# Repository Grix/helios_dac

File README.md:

# Helios Laser DAC
Digital to Analog Converter for laser projectors.

* https://bitlasers.com/helios-laser-dac/

Open source, low cost USB DAC for the ISP-DB25 (ILDA) laser protocol. Allows you to control an ILDA laser projector via computer over USB. Supports lots of third party software (see link above). This repository consists of:
* SDK for supporting the Helios USB and IDN DACs in your software (with examples in C++, Python and C#/.NET)
* Hardware (PCB schematic in KiCAD)
* Firmware (Atmel Studio project)
* Extras (firmware update tool, media etc.)

## Developer guide

#### Third party software integration

Navigate to the folder "sdk" to find the relevant code for interfacing with the Helios DAC in your software, and a readme with more detailed usage instructions. 

NEW: The C++ sdk has been updated to include IDN network support. This means that if you implement/update the Helios library in your application, it will also seamlessly enable support for any other network DAC using the IDN protocol, including the Helios OpenIDN adapter, StageMate ISP, and upcoming Helios products.
**Other libraries than the C++ one has not yet been updated with IDN support.**

The reference SDK is written in C++, in the subfolder "cpp". But libraries with exported functions that you can call from many languages such as python or C# are available, documented in HeliosDacAPI.h. You can also find examples of usage in the examples folder.

The C++ code depends on libusb. You can use the included libusb binary libraries for Win32, Mac or Linux, or you can build your own. You can find the libusb source on libusb.info, or binaries on https://sourceforge.net/projects/libusb/files/libusb-1.0/

If you wish to use the shared library, there are ready-made builds for Win32 (.dll) and 64-bit linux (.so) in the sdk folder. NB: Only the Windows binary is guaranteed to be up to date. For Mac and Linux it is recommended to build your own or use the C++ classes.

New: There is a native .NET library with example code in sdk/dotnet. HOWEVER, the C# library is not yet updated with IDN (network) support, so it is not recommended for general use yet.

If you are adding support for the Helios in your program, let me know and I can link it on the Helios' website.

Steps to compiling shared library (.so) for Linux based systems yourself is below. For macOS, try replacing ".so" with ".dylib". For Windows, there is a Visual Studio project in the source directory.

```shell
g++ -Wall -std=c++14 -fPIC -O2 -c HeliosDacAPI.cpp
g++ -Wall -std=c++14 -fPIC -O2 -c HeliosDac.cpp
g++ -shared -o libHeliosDacAPI.so HeliosDacAPI.o HeliosDac.o libusb-1.0.so
```
To use the device on Linux you either need root privileges or need to set up udev rules (see https://bitlasers.com/helios-laser-dac/). On Windows and Mac it should be plug and play.

A more detailed guide for compiling for Raspberry Pi (Linux ARM) is also available in the docs folder.

#### Hardware and firmware modification

The PCB is drawn in Kicad. The firmware is written and built with Atmel Studio for the ATSAM4S2B microcontroller.
**NB: The license for the hardware and firmware, unlike the software, does not permit the sale of manufactured units.**
New firmware can be uploaded to the device over USB. To do this, you must reset the "GPNVM1" bit in the flash memory, which will make the microcontroller boot to the SAM-BA bootloader. You can do this by sending a special interrupt packet to the DAC. You can then access the flash using Atmel's SAM-BA software or BOSSA. There is an automatic tool for firmware updating:

* Download the firmware updating tool (only for Windows as of now, Mac/Linux partially done): utility/FirmwareUpdater/cli/firmwareupdater_script.zip
* Unzip, plug in the DAC and run the file "flash.bat".
* Follow the instructions on the screen (you may need to unplug and replug the device a couple of times as instructed).

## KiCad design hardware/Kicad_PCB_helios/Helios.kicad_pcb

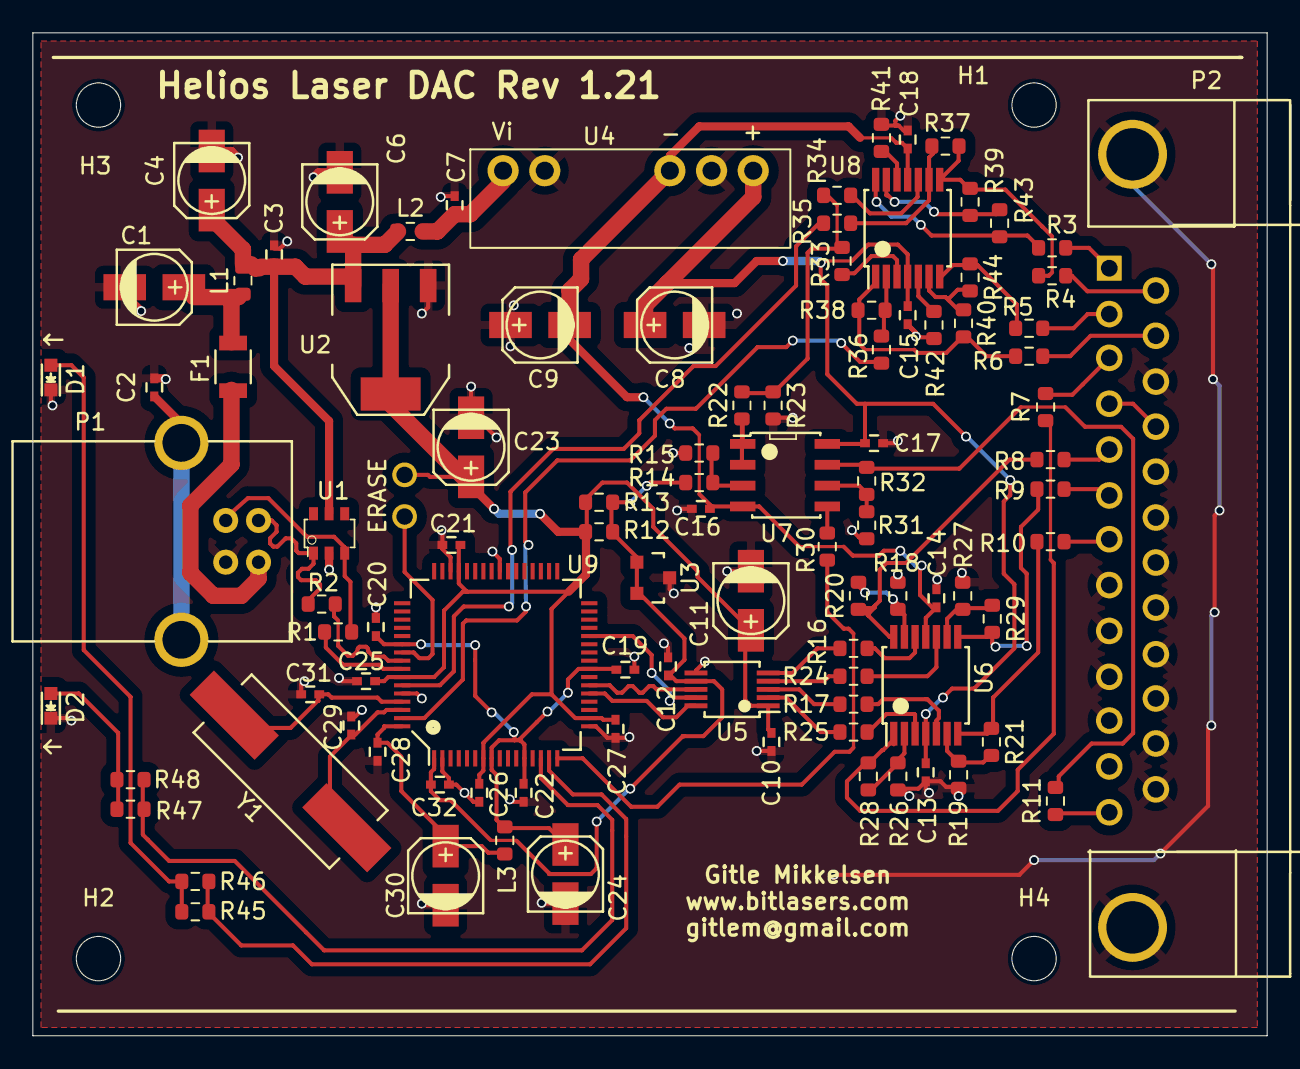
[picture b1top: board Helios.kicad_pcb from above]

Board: 2 copper layers, 75.2 x 61.1 mm, 102 parts (0 on the bottom side), 50 nets.

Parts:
C1, C4, C6, C8, C9, C11, C23, C24, C30: 4.7uF; c_elec_4x5.3
C2, C3, C7, C10, C13, C14, C15, C16, C17, C18, C19, C20, C21, C22, C25, C26, C27, C28: 100nF; C_0402
C12, C29, C31, C32: 13pF; C_0402
D1, D2: Led_Small; LED_0603
ERASE: CONN_01X02; PINHEAD1-2
F1: F_Small; R_1206
H1, H2, H3, H4: MountingHole; MountingHole_2.7mm_M2.5
L1, L2, L3: FILTER; R_0603_1608Metric
P1: USB_B
P2: CONN_01X25-SHIELD; DB25
R1, R2: 27; R_0603_1608Metric
R3, R4, R5, R6, R7, R8, R9, R10, R11, R12, R13: 150; R_0603_1608Metric
R14, R15, R18, R19, R20, R21, R23, R26, R27, R28, R29, R31, R37, R38, R39, R40, R43, R44: 10k; R_0603_1608Metric
R16, R17, R24, R25, R30, R32, R41, R42: 5.11k; R_0603_1608Metric
R22, R33, R34, R35, R36, R45, R46, R47, R48: 1.65k; R_0603_1608Metric
U1: IP4220CZ6; SOT457
U2: AP2114; SOT-223
U3: AN431B; SOT-23
U4: CRV1DxxxxSC
U5: DAC084S085C; MSOP-10_3x3mm_Pitch0.5mm
U6, U8: TL084_v; TSSOP-14_4.4x5mm_Pitch0.65mm
U7: LM358; SOIC-8_3.9x4.9mm_Pitch1.27mm
U9: ATSAM4S; LQFP-64_10x10mm_Pitch0.5mm
Y1: 16MHz 18pF; Crystal_HC49-SD_SMD

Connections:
/2.5V: C12.2, C32.1, R12.2, R13.2, R14.1, U3.1 (Cathode), U3.2 (Ref), U5.7 (Vrefin), U9.1 (ADVREF)
/3.3V: C10.1, C11.1, C21.1, C23.1, C25.1, C26.1, C27.1, ERASE.2, R12.1, R13.1, U2.2 (VOUT), U5.1 (Va), U9.7 (VDDIN), U9.18 (VDDIO), U9.45 (VDDIO), U9.58 (VDDIO)
/!SYNC: U5.9 (!SYNC), U9.28 (PA11/PGMM3)
/+9V: C8.1, C13.2, C15.2, C17.2, U4.7 (Vout+), U6.4 (Vcc), U7.8 (V+), U8.4 (Vcc)
/+B: R10.2, R21.1, U6.7 (Out)
/+G: R9.2, R29.1, U6.8 (Out)
/+Int: R7.2, R28.1, U6.1 (Out)
/+R: R8.2, R20.1, U6.14 (Out)
/+X: R3.2, R43.1, U8.14 (Out)
/+Y: R5.2, R44.1, U8.7 (Out)
/-9V: C9.2, C14.2, C16.2, C18.2, U4.5 (Vout-), U6.11 (Vee), U7.4 (V-), U8.11 (Vee)
/-X: R4.2, R37.1, R39.2, U8.8 (Out)
/-Y: R6.2, R38.1, R40.2, U8.1 (Out)
/Amplifiers/Offset: R22.2, R23.1, R33.2, R34.2
/B: R17.2, U5.3 (Voutb)
/D+: P1.3 (D+), R1.2, U1.3 (IO2)
/D-: P1.2 (D-), R2.2, U1.1 (IO1)
/G: R24.2, U5.4 (Voutc)
/Int: R25.2, U5.2 (Vouta)
/Interlock: P2.4, P2.17
/Microcontroller/D+: R1.1, U9.57 (DDP/PB11)
/Microcontroller/D-: R2.1, U9.56 (DDM/PB10)
/Microcontroller/ERASE: ERASE.1, U9.55 (ERASE/PB12)
/Microcontroller/PA22: R47.1, R48.1, U9.14 (PA22/PGMD10/AD9)
/Microcontroller/PA23: R45.1, R46.1, U9.15 (PA23/PGMD11)
/Microcontroller/VDDOUT: C19.1, C20.1, C22.1, C24.1, L3.1, U9.8 (VDDOUT), U9.12 (VDDCORE), U9.24 (VDDCORE), U9.54 (VDDCORE)
/Microcontroller/VDDPLL: C28.1, C30.1, L3.2, U9.64 (VDDPLL)
/Microcontroller/XIN: C29.1, U9.62 (XIN/PGMCK/PB9), Y1.1
/Microcontroller/XOUT: C31.1, U9.61 (XOUT/PB8), Y1.2
/R: R16.2, U5.5 (Voutd)
/SCLK: U5.10 (SCLK), U9.21 (PA14/PGMD2)
/Shutter: R30.2, U9.16 (PA20/PGMD8/AD3)
/Shutter_Out: R11.2, R32.1, U7.7
/VCC: C3.1, C4.1, C6.1, L1.2, L2.1, U1.5 (Vp), U2.3 (VIN)
/X: R35.2, U9.59 (PB13/DAC0)
/Y: R36.2, U9.63 (PB14/DAC1)
GND: C1.2, C2.2, C3.2, C4.2, C6.2, C7.2, C8.2, C9.1, C10.2, C11.2, C12.1, C13.1, C14.1, C15.1, C16.1, C17.1, C18.1, C19.2, C20.2, C21.2, C22.2, C23.2, C24.2, C25.2, C26.2, C27.2, C28.2, C29.2, C30.2, C31.2, C32.2, D1.1 (K), D2.1 (K), P1.4 (GND), P2.8, P2.9, P2.10, P2.11, P2.16, P2.18, P2.19, P2.20, P2.21, P2.22, P2.23, P2.24, P2.25, P2.26 (Shield), R15.2, R18.2, R19.2, R23.2, R26.2, R27.2, R31.1, R41.2, R42.2, U1.2 (GND), U2.1 (GND), U3.3 (Anode), U4.2 (GND), U4.6 (Vout0), U5.6 (GND), U9.2 (GND), U9.17 (GND), U9.40 (TST), U9.46 (GND), U9.60 (GND)
unnamed: C1.1, F1.2, L1.1
unnamed: F1.1, P1.1 (VCC)
unnamed: C2.1, P1.5 (shield)
unnamed: P2.1, R3.1
unnamed: P2.2, R5.1
unnamed: P2.3, R7.1
unnamed: P2.5, R8.1
unnamed: P2.6, R9.1
unnamed: P2.7, R10.1
unnamed: P2.13, R11.1
unnamed: P2.14, R4.1
unnamed: P2.15, R6.1
unnamed: C7.1, L2.2, U4.1 (Vin)

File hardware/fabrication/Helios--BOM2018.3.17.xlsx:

BOM
Manufacturer | Manufacturer Part Number | Designator | Qty | Description | Case | SMD ,BGA,LLC(QFN),OR TH | Top/Bottom | points | Total points | Note | Comments
Lelon | VE-4R7M1HTR-0405 | C1, C4, C6, C8, C9, C11, C23, C24, C30 | 9.0 | 4.7uF,50V,20%,4.00mmD*5.30mmH,2000Hrs@85℃ | 4.30mmL*4.30mmW | SMD | Top | 2.0 | 18
Yageo | CC0402KRX7R8BB104 | C2, C3, C7, C10, C13, C14, C15, C16, C17, C18, C19, C20, C21, C22, C25, C26, C2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 | 18.0 | 100nF,25V,10%,X7R,0402 | 0402 | SMD | Top | 2.0 | 36
Murata | GRM1555C1H130JA01D | C12, C29, C31, C32 | 4.0 | 13pF,50V,5%,C0G,0402 | 0402 | SMD | Top | 2.0 | 8
Yageo | RC0603JR-0727RL | R1, R2 | 2.0 | 27R,5%,1/10W,0603 | 0603 | SMD | Top | 2.0 | 4
Yageo | RC0603JR-07150RL | R3, R4, R5, R6, R7, R8, R9, R10, R11, R12, R13 | 11.0 | 150R,5%,1/10W,0603 | 0603 | SMD | Top | 2.0 | 22
Yageo | RC0603FR-071K65L | R22, R33, R34, R35, R36, R45, R46, R47, R48 | 9.0 | 1.65K,1%,1/10W,0603 | 0603 | SMD | Top | 2.0 | 18
Yageo | RC0603FR-075K11L | R32, R16, R17, R24, R25, R30, R41, R42 | 8.0 | 5.11K,1%,1/10W,0603 | 0603 | SMD | Top | 2.0 | 16
Yageo | RT0603BRD0710KL | R14, R15, R18, R19, R20, R21, R23, R26, R27, R28, R29, R31, R37, R38, R39, R40,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 | 18.0 | 10K,0.1%,1/10W,0603 | 0603 | SMD | Top | 2.0 | 36
ouleite | OLTEUSBFB-588 | P1 | 1.0 | USB,B type,90° | 16.30mmL*12.15mmW*11.00mmH | TH | Top | 6.0 | 6
TAD | DB-25F | P2 | 1.0 | Female,25 holes,90° | 53.10mmL*18.50mmW*12.55mmH | TH | Top | 27.0 | 27
NXP Semiconductors | IP4220CZ6,125 | U1 | 1.0 | IP4220CZ6,125,6-TSOP | 6-TSOP | SMD | Top | 6.0 | 6
Diodes Incorporated | AP2114H-3.3TRG1 | U2 | 1.0 | AP2114H-3.3TRG1,SOT-223 | SOT-223 | SMD | Top | 4.0 | 4
Diodes Incorporated | AN431AN-ATRG1 | U3 | 1.0 | AN431AN-ATRG1,SOT-23-3 | SOT-23-3 | SMD | Top | 3.0 | 3
XP Power | ISA0512-TR | U4 | 1.0 | 4.5Vin,5.5Vout/±12Vout,1W,15.20mmL*8.30mmW*7.30mmH | 15.20mmL*8.30mmW*7.30mmH | SMD | Top | 6.0 | 6.0
Texas Instruments | DAC084S085CIMM/NOPB | U5 | 1.0 | DAC084S085CIMM/NOPB,VSSOP-10 | VSSOP-10 | SMD | Top | 10.0 | 10
STMicroelectronics | TL084IPT | U6, U8 | 2.0 | TL084IPT,TSSOP-14 | TSSOP-14 | SMD | Top | 14.0 | 28
STMicroelectronics | LM358YDT | U7 | 1.0 | LM358YDT,SO-8 | SO-8 | SMD | Top | 8.0 | 8
Atmel | ATSAM4S2BA-AU | U9 | 1.0 | ATSAM4S2BA-AU,64-LQFP | 64-LQFP | SMD | Top | 64.0 | 64
Abracon | ABLS2-16.000MHZ-D4Y-T | Y1 | 1.0 | 16MHz,18pF,HC49/US | HC49/US | SMD | Top | 2.0 | 2
Bel Fuse | 0ZCJ0050FF2G | F1 | 1.0 | 8V,500mA,1206 | 1206 | SMD | Top | 2.0 | 2
TDK Corporation | MPZ1608B471ATA00 | L1, L2, L3 | 3.0 | 470R,1A,0603 | 0603 | SMD | Top | 2.0 | 6
Kingbright | APA1606SYCK | D1, D2 | 2.0 | Yellow,2V,150mcd,2-SMD | 2-SMD | SMD | Top | 2.0 | 4

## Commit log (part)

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2016-06-30 add kicad project
2016-07-09 temp driver and 7byte point structure firmware
2016-07-14 driver finished but untested
2016-07-18 GPIO signal wiring and USB IDs
2016-07-23 redone pcb, driver and firmware working-ish
2016-07-26 rev 1.1 pcb final
2016-07-29 fix BOM error
2016-08-03 experimenting with driver
2016-08-04 capacitors wrong polarity
2016-08-08 improve driver
2016-08-13 fix color amps error
2016-08-15 removed uneccessary resistors
2016-09-21 automatic winusb installation, not tested
2016-09-22 cleanup
2016-09-24 fix Stop() bug and winusb auto install working
2016-09-27 OLSC compatible driver
2016-09-29 media folder and tweaking interrupt transfers
2016-09-30 added delayed stop timer for reliability
2016-10-01 firmware version getter + some documentation
2016-10-02 Mac libusb binaries (not tested)
2016-10-07 reorganize folders
2016-10-15 custom naming of dac firmware working
2016-10-15 driver updated to support firmware v2
2016-10-16 backwards comp. fixed
2016-10-16 binaries
2016-10-16 started automated firmware flashing app based on sam-ba
2016-10-16 updated source in root
2016-10-21 cli firmware update script
2016-10-21 zipped firmware update script
2016-10-22 bossa firmware updating tool
2016-10-23 shrunk firmware with no mlong_calls to make bossac work
2016-10-26 added some niche functions to the API
2016-10-27 libusb 1.0.21
2016-10-29 updated root sdk source folder and organized better
2016-10-30 firmware tweaks, started sdk example
2016-11-01 Read different unique id
2016-11-26 example app tests all connected DACs instead of just one
2016-11-27 delay on initialization
2016-11-27 python example
2016-11-29 compile shared object library in order to use DAC on Linux using Python
2016-12-06 fix extern c, recompile so library with libusb and HeliosDac.cpp, split python examples on linux/windows version
2016-12-12 expand REDME.md file, add instructions how compile shared library with API
2016-12-21 optionally flipped X axis
2017-01-03 readme updated
2017-01-03 documentation tweaks
2017-01-10 fix a warning
2017-01-15 fixed jitter
2017-01-17 comments cleanup
2017-02-11 notice in license
2017-02-22 working on buffered status
2017-02-22 dropouts fixed
2017-02-22 more robust status transfer polling
2017-02-24 working on backwards compatibility and better exception handling
2017-02-26 mostly finished firmware+sdk v5 but bugs remain
2017-03-02 another strategy for status caching
2017-03-04 further sdk+firmware tweaks
2017-03-04 zipped test binaries
2017-03-05 more safety
2017-03-08 some debug, and length independent intrpt in transfer queries
2017-03-09 adjust the code to run on Linux, update shared library compilation instruction
2017-03-09 move library include from .cpp to .h files
2017-03-09 more experimentation
2017-03-11 major sdk rewrite
2017-03-11 working but not in lsx
2017-03-12 sdk backwards compatibility and robustness, plus new ASF version
2017-03-12 fixed thread not quitting when dac unplugged while playing, + cleanup
2017-03-13 zipped beta firmware with updating script
2017-03-19 better documentation in sdk header files
2017-03-20 updated example app
2017-03-20 updated bugfix in cpp example app
2017-03-26 no longer need to keep points buffer from being freed prematurely
2017-03-31 timeout check [chkpoint]
2017-06-07 less cpu usage
2017-06-08 blocking of WriteFrame() optional
2017-06-09 revert to explicit status query, + cleanup
2017-06-11 fix bug causing some frame sizes to fail + erronous flag constants in header
2017-06-12 add pps compensation to bug workaround
2017-06-13 some better commenting and cleanup
2017-06-14 pull
2017-06-14 sdk v6
2017-06-14 16bit xy in sdk
2017-06-30 better adherence to C++ rules
2017-06-30 inner namegetter passing by pointer
2017-07-12 add vref params to frames
2017-07-12 change frame of size allocs to make room for vref values
2017-08-21 img and udev note
2017-10-01 info paper
2017-10-29 small readme change
2017-12-20 update msvc project to 2017, with win64 build config
2017-12-20 folder name change for msvc source
2018-04-09 EzAudDac compatible api in driver
2018-04-27 libusb integrated
2018-05-25 small changes to info document
2018-06-06 change submodule to official libusb repo
2018-07-09 stdcall get/set name for vb
2018-07-15 fixed linux python example
2018-12-05 Add unique error codes for all error conditions.
2018-12-06 Add ability to set libusb debug log level
2018-12-06 Use correct device number in call to WriteFrame()
2018-12-06 Test for GetStatus() != 1 instead of GetStatus() == 0 so that errors aren't misinterpreted as ready status. Limit to 512 calls to GetStatus() before giving up.
2018-12-07 Copy linux_example.py fix to windows_example.py
2019-01-02 docs folder
2019-05-19 fix some outdated schematics
2019-08-28 Simplification of readme
2020-04-26 Started on dotnet nuget extension
2020-05-04 Wrote writeframe and getname functions in C# library
2020-10-12 modify HeliosDac.cpp in order to compile shared library under linux
2020-11-10 Readme updates, and some tweaks in EzAudDac compatibility API
2020-11-21 Continued on .NET driver, and fixed a compile error in c++ driver in windows
2020-11-22 More work on dotnet driver.
2021-01-02 Change doc for ubuntu 20.04 at RPi
    Fix path invalid at ubuntu 20.04
2021-01-29 Fix windows python example having too many points in a frame
2021-07-15 Add new photos
2021-08-22 Add diagnostics tool for usb Helios detection
2022-02-20 Russian translation of getting started doc
2022-08-21 Fix wrong frame buffer array size in dotnet implementation (but library still not working in windows)
2022-11-19 Working .NET SDK
2022-12-15 updated docs
2023-02-24 add 64-bit version of libusb windows binaries
2023-03-31 Fix dangling libusb thread after closing devices
2023-04-01 nuget package attributes
2023-04-30 Clarifying license
2023-04-30 Spelling
2023-05-21 Update docs
2023-10-15 Updated libusb windows binaries
2023-12-09 Update explanatory comment to new libusb version
2023-12-24 USB diagnosis tool binaries
2024-09-15 small docs update
2024-09-15 rename folder
2024-09-15 Reorganize and clean up SDK folder
2024-09-15 Include IDN files
2024-09-17 Basic IDN support working
2024-09-24 Changing strategy for variable resolution frames
2024-09-25 Legacy format IDN frame writing tested to work
2024-09-27 Move code to correct place
2024-10-12 Explicitly set shutter on C# example code
2024-10-13 Fix bugs in new IDN driver
2024-10-13 Add simulated status timing to IDN driver for compatibility
2024-10-25 Add support for getting firmware version and renaming IDN dacs
2024-10-25 Add support for renaming IDN DACs and fix bugs
2024-10-26 Separate max/min frame specs for USB and IDN, with subsampling for compatibility
2024-10-26 Modernized cpp app example, and fixed some bugs in IDN driver
2024-10-27 Fix compilation error on mac
2024-10-28 Readme update for IDN
2024-10-28 Implement new function in exported API, remove OLSC, and polish
2024-10-29 Fixed ezauddac exported wrapper
2024-10-30 Polish
2024-11-02 Fix IDN not properly stopping on closing device, and polish
2024-11-04 Compile dynamic libraries
2024-11-04 Integrated IDN support (#28)
    * Include IDN files
    * Basic IDN support working
    * Changing strategy for variable resolution frames
    * Legacy format IDN frame writing tested to work
    * Move code to correct place
    * Explicitly set shutter on C# example code
2024-11-23 Fix udp send buffer not big enough on certain OSes
2024-12-04 Started switch to IDN wave mode, but buggy
2024-12-05 Improve simulated timing
2024-12-05 Fix possible wave packet with too low point count.
2024-12-07 Misc polish
2024-12-08 Improved but still not good enough jitter. Also fix duplicate servers based on unit-id
2024-12-08 Checkpoint before trying ring buffer
2024-12-09 Major refactor, glitchy still
2024-12-10 Small tweaks. Glitchy, probably race condition
2024-12-11 Finally working well
2024-12-16 Added more functions for differentiating between USB and IDN devices
2024-12-18 Fix possible crash when closing device, and unix timing
2024-12-18 Revert accidental wrong mutex
2024-12-19 Sort device list and fix another possible crash when closing IDN device
2024-12-20 More tolerant timing if buffer underrun a little bit
2024-12-20 Don't count late waits when no frame is playing
2024-12-21 Fix possible stuck state after buffer underrun
2024-12-30 Final touches on documentation/comments
2025-01-03 Change IDN to wave mode, and more (#29)
    * Started switch to IDN wave mode, but buggy
    * Improve simulated timing
    * Fix possible wave packet with too low point count.
    * Misc polish
    * Improved but still not good enough jitter. Also fix duplicate servers based on unit-id
    * Checkpoint before trying ring buffer
2025-01-05 Fix some rare memory leaks and better syntax
2025-01-05 Fix potential race condition leading to division by zero
2025-01-13 rename plt-posix.c to .cpp
2025-01-13 rename plt-posix.c to .cpp (#30)
2025-04-01 Updated compile instructions for linux
2025-05-08 Fix visual studio windows example referencing posix-specific files
2025-06-23 Fix error in command for building on linux
2025-10-27 Rescanning
2025-10-27 Revert libusb update
2025-10-27 Better sleep in hot-plug example code
2025-10-27 Rescan fixes
2025-11-02 Don't verify connection during rescan if USB device was recently active
2025-11-28 Fix potential exception if rescanning usb after only scanning network initially
2025-11-28 Fix bug disrupting IDN timing if rescanning
2025-12-08 switch to new PSU on PCB. Fix bug in sdk example c++ app
2025-12-22 Update HeliosDac.cpp
    Fix crash if only opening USB
2026-01-01 Improve comments in driver and example code
2026-01-20 Award humble brag
2026-01-26 Fix bug with D1 in pcb
2026-02-01 rohs compliance doc
2026-02-17 Minor changes to fix compilation on MacOS
2026-03-10 Revert macOS specific packet handling
    Removed macOS specific handling for oversized UDP datagrams and adjusted logic for increasing max UDP packet size.
2026-03-11 fix(idn): initialize new IDN contexts in Unix scan path
    Restore missing Unix-side initialization of `isStoppedOrTimeout`,
    `packetNumFragments`, and `unitId` when creating IDN contexts.
    This matches Windows behavior and fixes rescan/device matching and
    initial packet sizing issues introduced during the rescan refactor.
2026-03-11 Minor changes to fix compilation on MacOS (#35)
    * Minor changes to fix compilation on MacOS
    * Revert macOS specific packet handling
    Removed macOS specific handling for oversized UDP datagrams and adjusted logic for increasing max UDP packet size.
    * fix(idn): initialize new IDN contexts in Unix scan path
    Restore missing Unix-side initialization of `isStoppedOrTimeout`,
    `packetNumFragments`, and `unitId` when creating IDN contexts.
2026-03-16 Fix USB teardown race on disconnect/reconnect
2026-03-17 Fix USB teardown race on disconnect/reconnect (#36)
2026-04-01 Tiny increase in scanning timeout
2026-04-24 refactor: combine Windows/Linux Python examples into unified module
    - Create platform-agnostic helios_example.py that detects OS for library loading
    - Extract HeliosPoint structure definition (shared by both examples)
    - Create reusable functions: load_library(), create_sample_frames(), play_frames()
    - Make module importable while preserving example functionality
    - Add docstrings and improve code quality
    - Support Windows, Linux, and macOS platforms
2026-04-24 Remove macOS library path configuration
    No macOS-compatible library provided, so remove example
2026-04-26 pylint cleanup
    - address "superfluous-parens" flagged lines
    - address "anomalous-backslash-in-string"
2026-04-28 pylint cleanup (#38)
    - address "superfluous-parens" flagged lines
    - address "anomalous-backslash-in-string"
2026-05-11 PCB v1.21
2026-05-11 Fix USB device with different depth being treated as the same as others on rescan
2026-05-11 Fix various bugs
